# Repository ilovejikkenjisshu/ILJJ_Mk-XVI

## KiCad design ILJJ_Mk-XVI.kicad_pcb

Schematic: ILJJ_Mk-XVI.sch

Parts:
C1: CP; CP_Radial_D8.0mm_P3.50mm
C2: C; C_Disc_D9.0mm_W5.0mm_P5.00mm
C3, C4, C5, C6, C8, C9: C; CP_Radial_D5.0mm_P2.00mm
C7: CP; CP_Radial_D6.3mm_P2.50mm
D1: POWER; LED_0603_HandSoldering
J1, J2, J4: AudioJack3_Ground; MJ-8435
J3: Barrel_Jack_Switch; BARREL_JACK
R1: R_LED; R_Axial_DIN0207_L6.3mm_D2.5mm_P2.54mm_Vertical
R2, R3, R4, R5, R6, R7, R8, R9, R14, R15, R16, R17: R; R_Axial_DIN0207_L6.3mm_D2.5mm_P2.54mm_Vertical
RV1, RV2, RV3: R_POT_Dual; RS30112AJA02
U1: NJM2114; DIP-8_W7.62mm_Socket

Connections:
4.5V: C7.1, R6.2, R7.2, U1.3 (+), U1.5 (+)
CH1_L: C3.1, RV1.2
CH1_R: C5.1, RV1.5
CH2_L: C4.1, RV2.2
CH2_R: C6.1, RV2.5
GND: C1.2, C2.2, C7.2, D1.1, J1.S, J2.S, J3.1, J4.S, R7.1, R16.1, R17.1, RV1.3, RV1.6, RV2.3, RV2.6, U1.4 (V-)
unnamed: C3.2, R2.2
unnamed: C4.2, R3.2
unnamed: C5.2, R4.2
unnamed: C6.2, R5.2
unnamed: C8.1, J4.T, R16.2
unnamed: C8.2, R14.2
unnamed: C9.1, J4.R, R17.2
unnamed: C9.2, R15.2
unnamed: D1.2, R1.2
unnamed: J1.R, RV1.4
unnamed: J1.T, RV1.1
unnamed: J2.R, RV2.4
unnamed: J2.T, RV2.1
unnamed: R2.1, R3.1, R8.2, U1.2 (-)
unnamed: R4.1, R5.1, R9.2, U1.6 (-)
unnamed: R8.1, RV3.1
unnamed: R9.1, RV3.4
unnamed: R14.1, RV3.2, RV3.3, U1.1
unnamed: R15.1, RV3.5, RV3.6, U1.7
VCC: C1.1, C2.1, J3.2, R1.1, R6.1, U1.8 (V+)

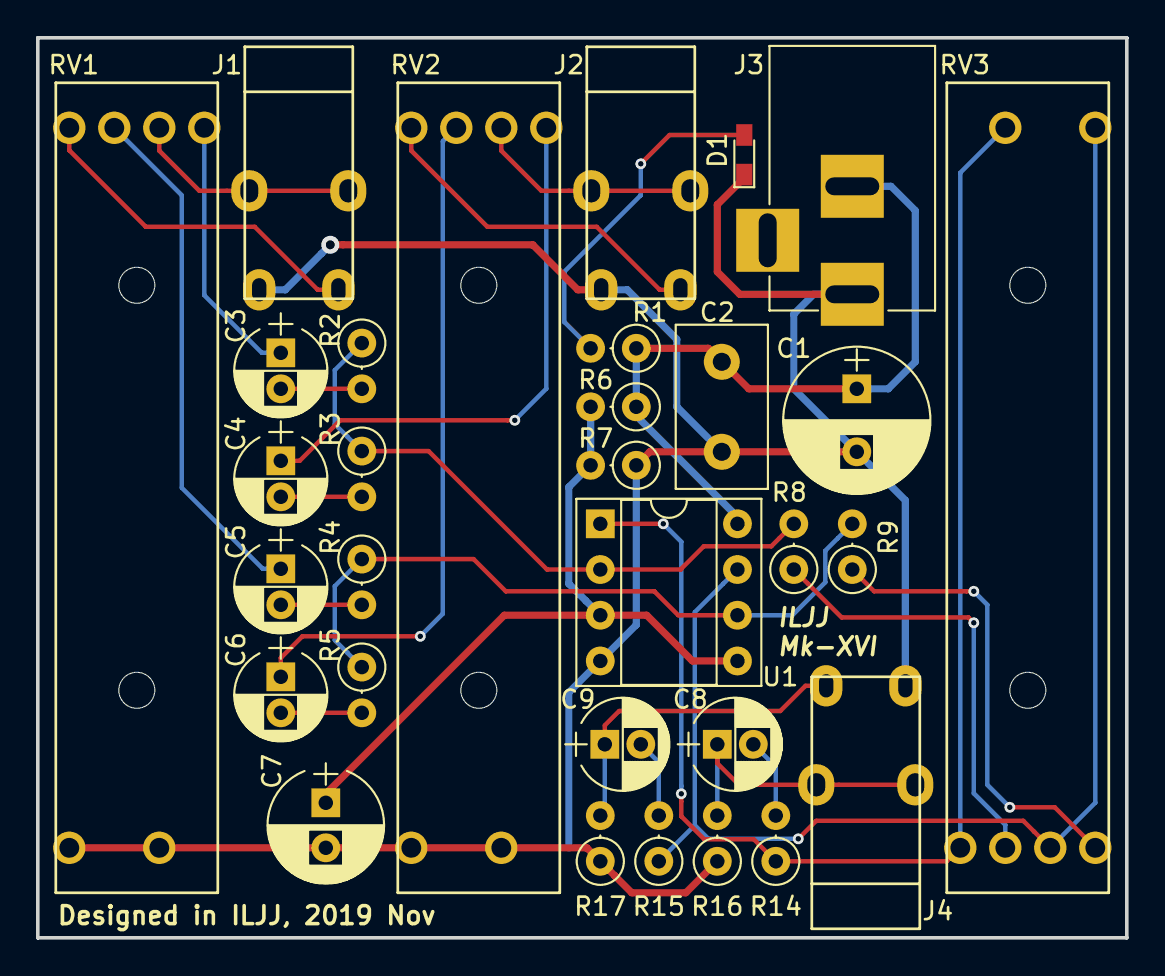
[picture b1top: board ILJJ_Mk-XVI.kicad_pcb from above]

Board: 2 copper layers, 60.5 x 50.0 mm, 31 parts (0 on the bottom side), 26 nets.

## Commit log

2019-11-14 initial commit
    sch only
2019-11-21 [change] footprint size
2019-11-21 [add] footprint for resistors and OPamps
2019-11-21 [change] polarity of DC jack
2019-11-21 [add] MJ-8435 TRS jack connector footprint
2019-11-21 [add] assigned footprints for connectors
2019-11-23 [add] footprints for RV
2019-11-23 [remove] 増幅回路を一段削減
    反転しててもええやろ(適当)
2019-11-30 [change] some footprints
2019-11-30 [add] 部品配置
2019-11-30 [add] 配線
2019-11-30 [update] リファレンスをちゃんと見えるように
2019-11-30 [update] U1とJ4のリファレンス印刷位置を変更
